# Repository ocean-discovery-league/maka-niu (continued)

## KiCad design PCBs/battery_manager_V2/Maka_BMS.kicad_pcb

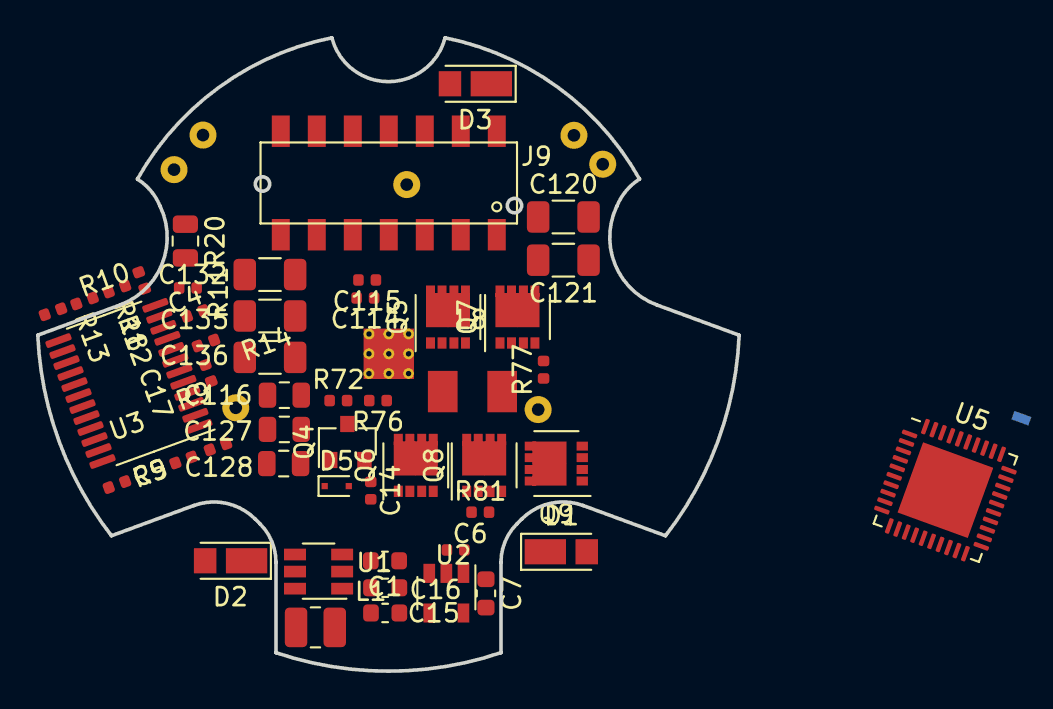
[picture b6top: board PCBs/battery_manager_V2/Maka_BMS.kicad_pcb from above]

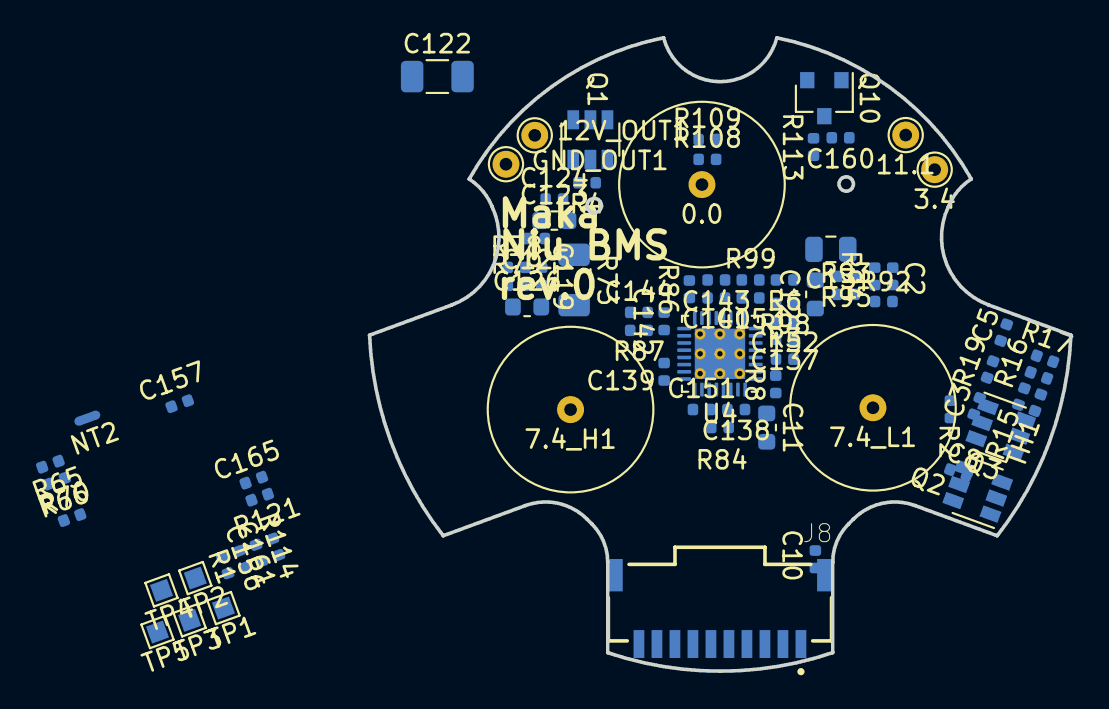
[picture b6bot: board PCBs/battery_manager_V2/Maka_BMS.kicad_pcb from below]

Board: 4 copper layers, 39.0 x 35.2 mm, 128 parts (79 on the bottom side), 89 nets, no tracks yet.

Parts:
0.0: 0; TruHole_Batter_Contact_Pad_with_9mm_clear
3.4: 3.4; TestPoint_THTPad_D1.5mm_Drill0.7mm
7.4_H1, 7.4_L1: 7.4; TruHole_Batter_Contact_Pad_with_9mm_clear
11.1: 11.1; TestPoint_THTPad_D1.5mm_Drill0.7mm
12V_OUT1: 12V_OUT; TestPoint_THTPad_D1.5mm_Drill0.7mm
C1, C15, C16, C123, C126: 10uF; C_0603_1608Metric
C2, C152, C153: 100pF; C_0402_1005Metric
C3, C4, C5, C10, C17, C119, C124, C156, C157: 0.1uF; C_0402_1005Metric
C6, C8, C9, C125, C137: 1uF; C_0402_1005Metric
C7: 4.7uF; C_0603_1608Metric
C11, C12: 0.033uF; C_0603_1608Metric
C13: 0.47uF; C_0805_2012Metric
C14, C138, C139: 0.047uF; C_0402_1005Metric
C114: 0.01uF; C_0402_1005Metric
C115, C160: 1000pF; C_0402_1005Metric
C116, C127, C128: 10uF; C_0805_2012Metric
C120, C136: 56uF; C_1206_3216Metric
C121, C122: 47uF; C_1206_3216Metric
C132, C135: 22uF; C_1206_3216Metric
C140: 33pF; C_0402_1005Metric
C142: 15pF; C_0402_1005Metric
C143: 1800pF; C_0402_1005Metric
C144: 680pF; C_0402_1005Metric
C151: 2.2uF; C_0402_1005Metric
C161, C165: 47pF; C_0402_1005Metric
D1, D2, D3: D_Schottky; D_SOD-123EP
D5: BAS5202VH6327; D_SC-79
GND_OUT1: GND_OUT; TestPoint_THTPad_D1.5mm_Drill0.7mm
J8: T1M-10-F-SH-L-K; SAMTEC_T1M-10-F-SH-L-K
J9: Molex 087340-1424; Molex_87340-1424_B
L1: 4.7uH; L_1008_2520Metric
L8: 2.2uH_Core_Iron; L_4.95x4.95_H2
NT2: Net-Tie_2; NetTie-2_SMD_Pad0.5mm
Q1, Q2, Q3: FDC645N; SOT-23-6_mosfet
Q4: BC817-16LT1G; SOT-23
Q5, Q6, Q7, Q8: CSD17308Q3; VSON-8_3.3x3.3mm_P0.65mm_NexFET
Q9: CSD25404Q3; VSON-8_3.3x3.3mm_P0.65mm_NexFET
Q10: DMG1012UW-7; SOT-23
R1, R16, R65, R66, R70, R95: 100K; R_0402_1005Metric
R2, R4, R5, R9, R13, R14, R19: 1K; R_0402_1005Metric
R3, R6: 4.99; R_0402_1005Metric
R8: 1; R_0402_1005Metric
R10, R15, R17, R87, R108, R109: 10K; R_0402_1005Metric
R11, R12: 1M; R_0402_1005Metric
R18: 470K; R_0402_1005Metric
R20: 0.02; R_0805_2012Metric
R72: 0.01; R_0402_1005Metric
R73: 0.01; R_1206_3216Metric
R76, R77, R81: 0; R_0402_1005Metric
R78, R79, R84, R114, R121: 10; R_0402_1005Metric
R86: 40.2K; R_0402_1005Metric
R92: 383K; R_0402_1005Metric
R93: 53.6K; R_0402_1005Metric
R94: 221K; R_0402_1005Metric
R98: 137K; R_0402_1005Metric
R99, R113: 30.1K; R_0402_1005Metric
TH1: 10K; R_0402_1005Metric
TP1: DSG_LED; TestPoint_Pad_1.0x1.0mm
TP2: BT1_LED; TestPoint_Pad_1.0x1.0mm
TP3: BT2_LED; TestPoint_Pad_1.0x1.0mm
TP4: BT3LED; TestPoint_Pad_1.0x1.0mm
TP5: BT4LED; TestPoint_Pad_1.0x1.0mm
U1: AP63205; TSOT-23-6
U2: TPS70933DBV; SOT-23-5
U3: BQ77915; TSSOP-24_4.4x7.8mm_P0.65mm
U4: BQ25703A_alt; Texas_S-PWQFN-N32_EP2.8x2.8mm_ThermalVias
U5: MSP430G2955IRHA40; Texas_S-PVQFN-N40_EP4.15x4.15mm

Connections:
+3.3VP: J9.7, Q10.2
+3V3: C7.2, C156.2, C157.2, J8.09, Q10.3, R65.2, R66.2, R108.1, R109.1, R113.2, U2.5, U5.14, U5.38, U5.39
+5V: C15.2, C16.2, J8.02, L1.2, U1.1
+BATT: 11.1.1, C119.2, C126.2, D2.2, R5.2, R9.2, R73.2, R79.2
-BATT: 0.0.1, C4.1, C5.2, C8.1, C9.2, R16.1, R17.1, R19.2, R20.2, TH1.1, U3.9, U3.10, U3.20, U3.23, U3.24
/A_EN: R70.2, U5.26
/BATDRVb: Q9.4, U4.21
/CHG_ACN: C114.2, C115.2, Q5.5, R3.2, R8.2, R72.1
/CHG_OK: R66.1, U4.4, U5.29
/CHG_PRC: R65.1, U4.11, U5.30
/CHG_SRN: R79.1, U4.19
/CHG_SRP: R78.1, U4.20
/COMP1: C140.2, R86.1, U4.16
/COMP2: C142.2, C144.2, U4.17
/DSG_EN: R1.1, U4.5, U5.12
/HB_HDV1: R76.2, U4.31
/HB_HDV2: R77.1, U4.24
/HB_HVDD1: C138.2, U4.30
/HB_HVDD2: C139.2, U4.25
/HB_LDV2: R81.1, U4.26
/HB_LG1: D5.1, Q4.1, U4.29
/HB_SW1: C138.1, L8.1, Q5.1, Q5.2, Q5.3, Q6.5, U4.32
/HB_SW2: C139.1, L8.2, Q7.1, Q7.2, Q7.3, Q8.5, U4.23
/IBAT: C153.2, U4.9, U5.7
/IPORT: C152.2, R98.2, U4.8, U5.6
/PSYS: R99.2, U4.10, U5.8
/REGN: C14.2, C151.2, Q4.3, R84.2, U4.28
/VDDA: C137.2, R84.1, R92.2, R93.2, U4.7
/VSYS: C120.1, C121.2, C122.2, C123.2, C124.2, Q7.5, Q9.5, U4.22
EN_3V3: Q10.1, U5.28
EN_5V0: U1.2, U5.40
EN_12V_G: R4.1, U5.3
EOC_KELLER: J8.05, J9.9
Earth: C1.1, C6.1, C7.1, C11.2, C12.1, C13.1, C14.1, C15.1, C16.1, C114.1, C115.1, C116.2, C120.2, C121.1, C122.1, C123.1, C124.1, C125.1, C126.1, C127.2, C128.2, C132.2, C135.2, C136.2, C137.1, C140.1, C142.1, C143.1, C151.1, C152.1, C153.1, C160.1, J8.01, J9.13, J9.14, NT2.2, Q1.3, Q3.3, Q6.1, Q6.2, Q6.3, Q8.1, Q8.2, Q8.3, R12.1, R18.1, R87.1, R98.1, R99.1, U1.4, U2.2, U4.14, U4.27, U4.33
GNDA: C156.1, C157.1, C161.1, C165.1, NT2.1, R1.2, R70.1, U5.1, U5.4, U5.13, U5.31, U5.41
GPS_INT: J8.07, J9.8
IMU_INT: J8.08, J9.10
unnamed: 3.4.1, R14.2
unnamed: 7.4_L1.1, R2.2
unnamed: 12V_OUT1.1, C1.2, C6.2, D1.1, D2.1, D3.1, U1.3, U2.1
unnamed: C2.1, R92.1, R94.2, U4.6
unnamed: C2.2, R94.1, R95.1
unnamed: C3.1, C4.2, R14.1, U3.7
unnamed: C5.1, R19.1, U3.8
unnamed: C8.2, R5.1, U3.1, U3.22
unnamed: C9.1, U3.2
unnamed: C10.1, L1.1, U1.5
unnamed: C10.2, U1.6
unnamed: C11.1, R3.1, U4.2
unnamed: C12.2, R6.1, U4.3
unnamed: C13.2, R8.1, U4.1
unnamed: C3.2, C17.1, R2.1, U3.6
unnamed: C17.2, R9.1, U3.3, U3.4, U3.5
unnamed: C119.1, C125.2, Q9.1, R73.1, R78.2
unnamed: C143.2, R86.2
unnamed: C144.1, R87.2
unnamed: D3.2, GND_OUT1.1, Q1.1
unnamed: D5.2, Q4.2, Q6.4
unnamed: Q1.2, R4.2
unnamed: Q2.1, Q3.1
unnamed: Q2.2, R10.1, R11.2
unnamed: Q2.3, R11.1, R20.1, U3.11
unnamed: Q3.2, R12.2, R13.1
unnamed: Q5.4, R76.1
unnamed: Q7.4, R77.2
unnamed: Q8.4, R81.2
unnamed: R10.2, U3.12
unnamed: R13.2, U3.13
unnamed: R15.1, TH1.2, U3.18
unnamed: R15.2, U3.19
unnamed: R16.2, U3.17
unnamed: R17.2, U3.16
unnamed: R18.2, U3.14
unnamed: R93.1, R95.2, U4.18
unnamed: R114.2, U5.11
unnamed: R121.2, U5.10
unnamed: TP1.1, U5.15
unnamed: TP2.1, U5.16
unnamed: TP3.1, U5.17
unnamed: TP4.1, U5.18
unnamed: TP5.1, U5.19
SBWTCK: J9.11, U5.37
SBWTDI: C160.2, J9.12, R113.1, U5.5
SCL: C161.2, J8.03, J9.5, R109.2, R114.1, U4.13
SDA: C165.2, J8.04, J9.6, R108.2, R121.1, U4.12
VBUS: C116.1, C127.1, C128.1, C132.1, C135.1, C136.1, D1.2, J9.1, J9.2, R6.2, R72.2
~INT~: J8.06, J9.3
~SHT_DWN_SIG~: J8.10, U5.36
~TS_EOC~: J9.4, U5.2

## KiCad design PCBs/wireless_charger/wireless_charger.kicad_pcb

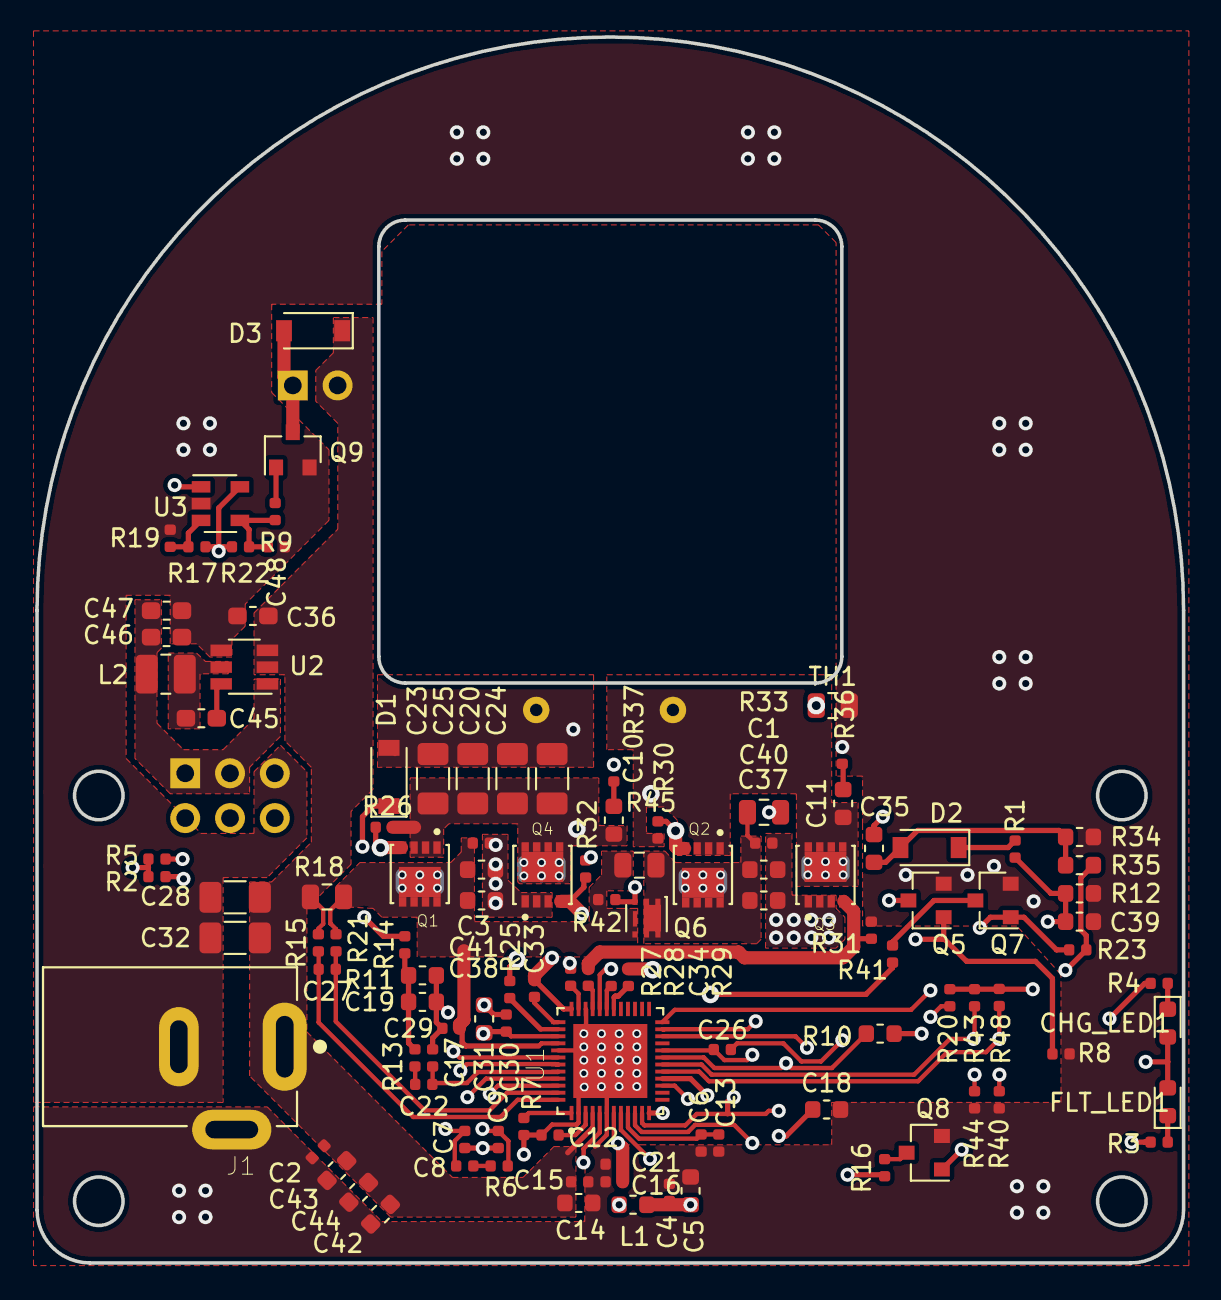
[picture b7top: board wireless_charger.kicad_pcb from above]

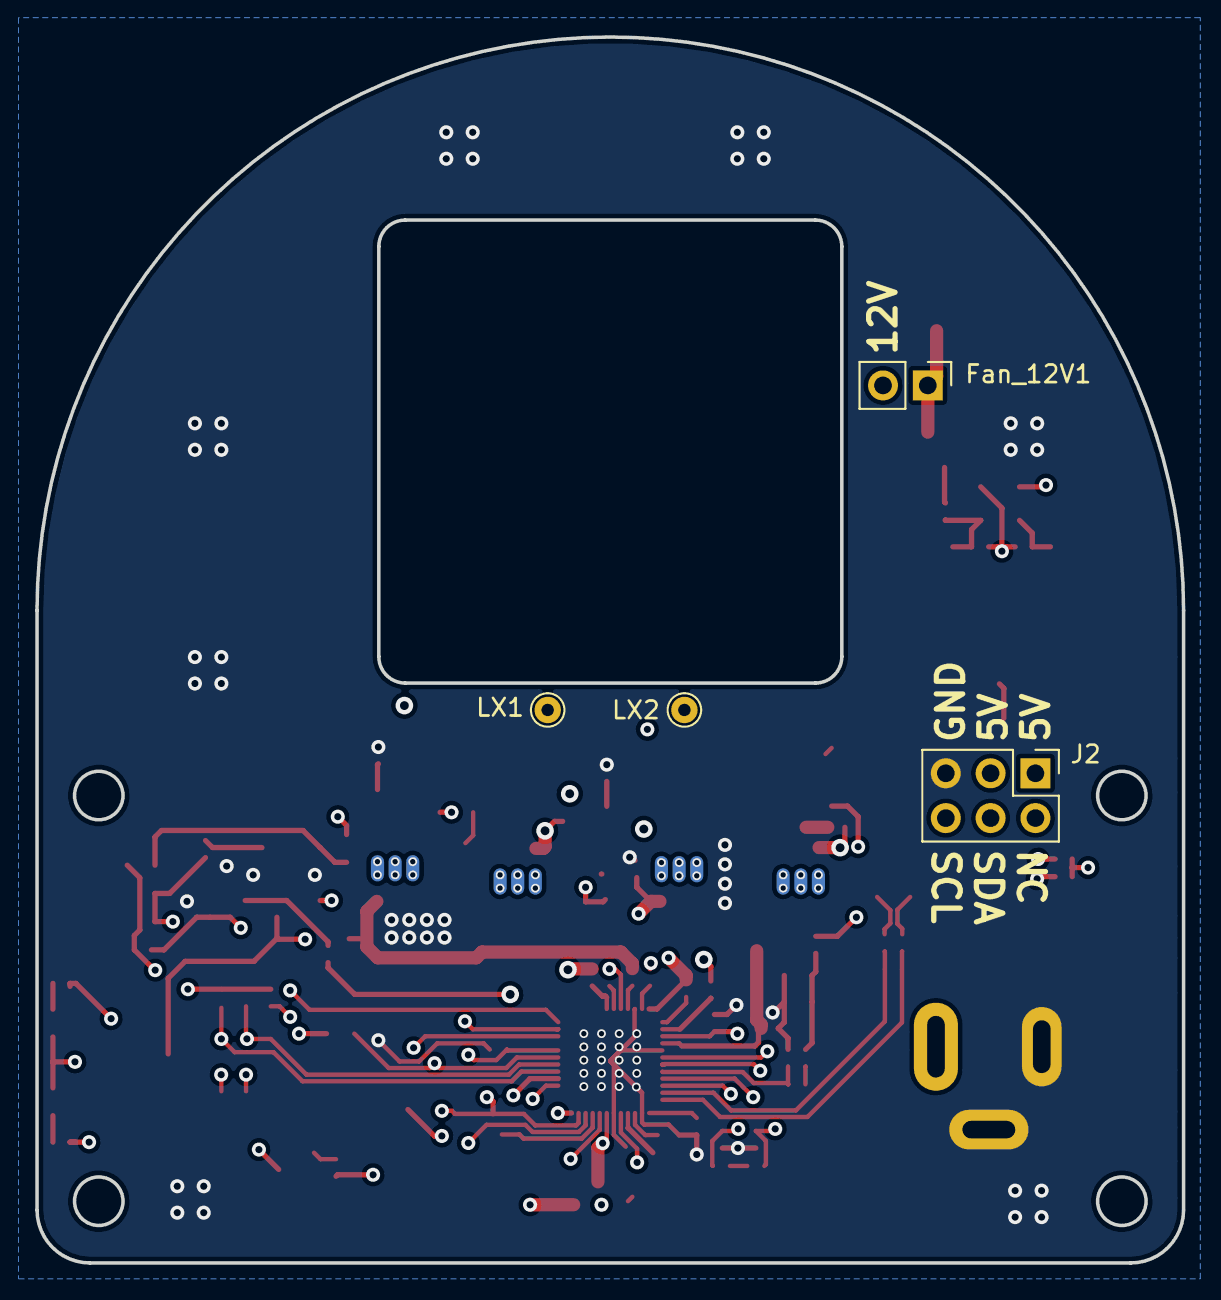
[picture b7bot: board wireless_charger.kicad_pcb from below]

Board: 4 copper layers, 65.0 x 69.5 mm, 116 parts (4 on the bottom side), 61 nets.

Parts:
C1, C2, C3, C4, C13, C15, C21, C26, C29, C30, C33, C34: 0.1uF; C_0402_1005Metric
C5, C14, C31, C37, C38, C40, C41: 10uF; C_0603_1608Metric
C6, C12, C16, C27: 1uF; C_0402_1005Metric
C7, C9: 56pF; C_0402_1005Metric
C8: 6.8nF; C_0402_1005Metric
C10, C11: 22nF; C_0603_1608Metric
C17: 680pF; C_0402_1005Metric
C18: 1nF; C_0603_1608Metric
C19, C35, C39: 5.6nF; C_0603_1608Metric
C20, C23, C24: 100nF; C_1206_3216Metric
C22: 22nF; C_0402_1005Metric
C25: 68nF; C_1206_3216Metric
C28, C32: 22uF; C_1206_3216Metric
C36, C46, C47: 10uF; C_0603_1608Metric_Pad1.05x0.95mm_HandSolder
C42: 0.1uF; C_0603_1608Metric
C43: 1uF; C_0603_1608Metric
C44: 4.7uF; C_0603_1608Metric
C45: 100nF; C_0603_1608Metric_Pad1.05x0.95mm_HandSolder
C48: 15pF; C_0402_1005Metric
CHG_LED1: GREEN; LED_0603_1608Metric
D1, D2: BAV21W; D_SOD-123
D3: MBR0530; D_SOD-123
FLT_LED1: RED; LED_0603_1608Metric
Fan_12V1: Conn_01x02; PinHeader_1x02_P2.54mm_Vertical
J1: Barrel_Jack_Switch; CUI_PJ-002AH
J2: Pi_Receiver; PinHeader_2x03_P2.54mm_Vertical
L1: 4.7uH; L_0603_1608Metric
L2: 4.7uH; L_1008_2520Metric
LX1, LX2: MountingHole_Pad; TestPoint_THTPad_D1.5mm_Drill0.7mm
Q1, Q2, Q3, Q4: DMG7430LFG; TRANS_DMP3017SFGQ-7_b
Q5, Q7, Q8: 2N7002; SOT-23
Q6: SiA453EDJ; Vishay_PowerPAK_SC70-6L_Single
Q9: NTR4003N; SOT-23
R1, R3, R7, R9: 1K; R_0402_1005Metric
R2, R5, R6, R13, R16, R19, R20, R22, R23, R41, R42, R43, R48: 10K; R_0402_1005Metric
R4: 680; R_0402_1005Metric
R8, R26, R30, R31, R32: 100K; R_0402_1005Metric
R10, R12: 390K; R_0603_1608Metric
R11, R35: 200K; R_0603_1608Metric
R14: 2.4K; R_0402_1005Metric
R15, R21: 10; R_0402_1005Metric
R17: 17.8; R_0402_1005Metric
R18: 0.02; R_0805_2012Metric
R25, R27, R28, R29: 12; R_0402_1005Metric
R33: 3; R_0805_2012Metric
R34: 100K; R_0603_1608Metric
R36, R37: 0.1; R_0402_1005Metric
R40: 14.3; R_0402_1005Metric
R44: 15.8K; R_0402_1005Metric
R45: 220; R_0805_2012Metric
TH1: 10K Thermistor; R_0805_2012Metric
U1: P9242-RNDGI8; QFN40P600X600X100-49N
U2: AP63205; TSOT-23-6
U3: LMV331; SOT-23-5

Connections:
+5V: C46.2, C47.2, J2.1, J2.3, L2.2, U2.1
/SCL: J2.6, R2.1, U1.15
/SDA: J2.4, R5.1, U1.16
/TS: C26.2, R20.2, TH1.1, U1.20, U3.1
/coil1: C11.2, C34.2, LX1.1, Q2.1, Q3.3, R30.1, U1.32
/coil2: C20.2, C23.2, C24.2, C25.2, C35.2, D1.2, LX2.1
Earth: C1.1, C2.2, C3.1, C4.1, C5.1, C6.1, C7.1, C9.1, C12.2, C13.1, C14.1, C15.1, C16.1, C17.1, C18.1, C19.1, C21.1, C26.1, C28.1, C29.1, C30.1, C31.1, C32.1, C36.1, C37.1, C38.1, C39.1, C40.1, C41.1, C42.2, C43.2, C44.2, C46.1, C47.1, C48.1, J1.2, J1.3, J2.5, Q3.1, Q4.1, Q5.2, Q7.2, Q8.2, Q9.2, R7.2, R8.1, R11.2, R12.2, R19.1, R31.1, R32.1, R34.2, R36.1, R37.1, R40.1, R44.1, TH1.2, U1.2, U1.6, U1.34, U1.41, U1.49, U2.4, U3.2
ISNS_H: C27.1, R15.1, U1.48
ISNS_L: C27.2, R21.1, U1.47
LDO18: C6.2, C13.2, U1.9
LDO33: C16.2, C21.2, CHG_LED1.2, FLT_LED1.2, R2.2, R5.2, R17.2, R20.1, R22.1, R23.2, R35.2, R43.2, R48.2, U1.7, U1.12, U3.5
unnamed: C1.2, C37.2, C40.2, Q2.3, Q6.1, R33.2, R45.1
unnamed: C7.2, C8.2, U1.45
unnamed: C8.1, R6.1
unnamed: C9.2, R6.2, U1.46
unnamed: C10.1, R37.2
unnamed: C10.2, C20.1, C23.1, C24.1, C25.1, C33.2, Q1.1, Q4.3, R26.1, U1.36
unnamed: C11.1, R36.2
unnamed: C12.1, U1.3
unnamed: C17.2, C22.1, U1.44
unnamed: C19.2, R11.1, R13.2, R14.1
unnamed: C22.2, R13.1
unnamed: C3.2, C29.2, C38.2, C41.2, Q1.3, Q6.4, R18.1, R21.2, R42.2, R45.2, U1.40
unnamed: C33.1, U1.37
unnamed: C34.1, U1.31
unnamed: C35.1, D2.2, R34.1, R35.1
unnamed: C39.2, R1.1, R10.1, R12.1
unnamed: C45.1, L2.1, U2.5
unnamed: C45.2, U2.6
unnamed: C48.2, R9.1, R22.2, U3.4
unnamed: CHG_LED1.1, R4.2
unnamed: D1.1, R14.2
unnamed: D2.1, R1.2
unnamed: D3.2, Fan_12V1.1, Q9.3
unnamed: FLT_LED1.1, R3.2
unnamed: L1.2, U1.5
unnamed: Q1.2, R25.1, R26.2
unnamed: Q2.2, R29.1, R30.2
unnamed: Q3.2, R28.1, R31.2
unnamed: Q4.2, R27.1, R32.2
unnamed: Q5.3, R33.1
unnamed: Q6.3, R41.2, R42.1
unnamed: Q7.3, R41.1
unnamed: Q8.3, R16.2
unnamed: Q9.1, R9.2
unnamed: R3.1, U1.10
unnamed: R4.1, U1.11
unnamed: R7.1, U1.1
unnamed: R17.1, R19.2, U3.3
unnamed: R25.2, U1.38
unnamed: R27.2, U1.35
unnamed: R28.2, U1.33
unnamed: R29.2, U1.30
unnamed: R40.2, R48.1, U1.17
unnamed: R43.1, R44.2, U1.18
OVP_CTL: Q8.1, U1.22
Q_DRV1: Q5.1, R8.2, U1.23
Q_DRV2: Q7.1, R23.1, U1.24
VCC_5V: C4.2, C5.2, C30.2, C31.2, L1.1, U1.8, U1.39
VCOIL_OV: C18.2, R10.2, R16.1, U1.19
VIN: C2.1, C14.2, C15.2, C28.2, C32.2, C36.2, C42.1, C43.1, C44.1, D3.1, Fan_12V1.2, J1.1, R15.2, R18.2, U1.4, U2.2, U2.3

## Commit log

2020-06-24 Lui's first commit, addign a python script to record video on the Pi Zero with aa camera module, with timestamp overlay. This could be used in Maka Niu to overlay temperature, depth etc. Also adding 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
2020-06-24 reorganized directory for future use
2020-07-07 Add files via upload
    Uploads a specified file to Tator
2020-07-07 Add files via upload
    Bash file to upload all mp4 files in directory (Calls TatorUpload.py with given arguments)
2020-07-13 added the kellerLD library, and a version of the example with a depth estimation based on pressure.
2020-07-17 Added a more complex python program Mode_dial_with_button for testing the the new hall sensor ring togethr with the new dial lthat incorporates a button
2020-07-31 added XM1110_example.py and supporting library. Example gets NMEA data from XM1111 via I2C and updates class objects with relevant info.
2020-08-13 Added the hall ring magnetic dial Kicad project
2020-08-13 added the battery management board kicad project
2020-08-13 Icreased trace thickness and rerouted higher freq and power paths in the battery management board
2020-08-14 added documenation folder and pushed 1st Power Distribution Chart
2020-08-14 Updated index.php: can access program.php, upload w button
2020-08-14 Updated index.php w program.php link and upload button
2020-08-14 Scaffold of page for user programmed missions
2020-08-14 added the maka niu general build BOM, and the maka niu build guide
2020-08-14 Chart of the code for program.php
    Displays all of the possible code blocks user would want to create and the respective strings for use in translating into python, and the string used to display html components
2020-08-14 changed current sensing resistor values on the BMS board to appropriately trip short and over current situations, adn to appropriately end incomig charge
2020-08-18 assigned digikey part to every item in battery management schematic, and created BOM
2020-08-31 Add files via upload
    Visual Representation and estimation calculation
2020-08-31 Add files via upload
    Documentation for Visual Representation and estimation calculations
2020-09-03 adding in progress pcb design files for the charging Station
2020-09-22 completed the wireless charger PCB design as rev 0. bom is compiled
2020-09-25 minor updating on BOM organization
2020-09-25 safety merge
2020-10-02 adding LED patterns simplified.
2020-10-22 first attempt at adding RPiCWI as a submodule
2020-10-23 added makaniu BMS board V2, and wayfinders 6cell BMS.
2020-11-22 Added haptic feedback to the Mode Dial python script
2020-11-22 updates to battery managemennt wayfinder boards, and makaniu hall sensor ring and BMS
2020-11-23 Fine of haptic feedback. new click, double click, burst, and dial change incorporated
2020-11-23 bit more fine tuning on haptic feedback. The clicks are nicer, but too hard notice by feel. Hearing them gives the illusion that they are enough, but with noise canceling headphones on, I can barely 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
2020-12-04 added comments for GPIOS
2020-12-04 Minor notes on BMS pcb project
2020-12-04 added Maka Niu User Flowchart.pdf in documentation
2020-12-07 Added a program called MakaNiu.py that begins to pull and incroporate all the peripheral hardware. Mode and button control, GPS, and image and video capture all working
2021-01-15 commented out drv vibration code because it causes crash if device not present
2021-01-18 MakaNiu.py program updated to include pressure info, as well as battery info, although it is disabled due to instability
2021-01-18 Lengthened update time for GPS and pressure to once every ten seconds, so that it interferes less with button presses. Need to bring in threads maybe, thou mixing I2c is scary. Also added a program t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
2021-01-18 improved timing interference between buttons and all the i2c time
2021-01-18 added a shell script to run python program with error log
2021-01-21 added try format to keller i2c comms to avoid occasional crash.
2021-01-22 All interfaces now protected with try/except method to prevent crashes. Program will run if any of these are missing. If all is present and talking, at startup, a green LED will hold for 3 seconds. A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
2021-01-22 added crash protection on DRV haptic feedback i2c. now Pi runs even if no interface connected.
2021-01-22 added the error log save destination on git
2021-01-25 Due to a a sepcific startup issue that emerged with introduciton of spi1, the shutdown pin has been switched with the enable endcap pin. Also added the enable endcap feature.
2021-01-26 added green light flash for GPS fix
2021-02-02 Incorporated date time from GPS. Required some changes in the gps libraries.
2021-02-02 Add files via upload
    Silkscreen modified for production
2021-02-02 Add files via upload
    Updated silkscreens
2021-02-02 Add files via upload
    Finalized for production
2021-02-02 Add files via upload
    added documentation for endcap PCB
2021-02-02 incorporated ability to name image files
2021-02-04 sped up shut down sequence
2021-02-05 added crash prptection with try for gps data
2021-02-05 added Pi video file naming, and added serial number to img and video naming.
2021-02-12 added sensor data file creation for videos
2021-02-12 heavy addition and cleanup of comments
2021-02-13 added creation of data file in missions
2021-02-13 added sensor data saving for images and burst images. Addressed a bug where burst photos also start a video.
2021-02-15 Added system clock entry in the sensor data files so that the separate mission manager program can easily read entry time
2021-02-17 implemented rotating data and error logging
2021-02-18 Added IMU sensor data collection and write to sensor files
2021-02-19 added battery power indication in wifi mode when battery pressed
2021-02-22 added use of pi os hostname in filenaming
2021-02-22 removed import of makaniu_config.py for now, not currently used
2021-02-22 sensor file writing now has has flush built into every print to update the files faster, and mode changes are written to a status file in log directory for easy read by other running software
2021-02-23 software/hardware fix of imu address bug. pin address was floating in hardware, so hardware fix sets the address to 0x69. Software follows the correction
2021-02-24 fixed datestamp for special case gns2 data in photo captures
2021-02-25 updated the repo with all latest pcb changes for the 6cell bms, 3cell bms, and for the wireless charger. Also added sensor data readme filein the same directory as the makaniu python program
2021-04-04 disabled led and hdmi cuttoff after some time, till this feature is really needed feo deployment
2021-04-08 added device id and mac address data to the top of each generated sensor file
2021-05-17 converted to non-dos eols, flush stdout on upload progress reports
2021-05-21 hacked in support for uploading attachments
2021-05-21 added link to attachments upload tutorial
2021-05-25 upload to folder named by hostname
2021-05-26 Reinstated LED and HDMI shutdown for poer saving, and reduced burst photo rate to 2hz to sidestep a bug that caused missing thumbnail images
2021-07-08 implemented keller depth offset background calibration that uses gps fix as reference for 0 depth.
2021-07-08 implemented clock update from gps even without a fix. Also disabled wifi in non wifi modes for power saving
2021-11-17 created a script locker folder to hold code that needs to be manually copied to other places. Also upgraded the wifi disbale code to close the access point.
2021-11-17 code version print changed to 1.03, to make it a little easier to track if users are up to date
2021-12-10 added a dimmensioned drawing of the Maka Niu Housing in the documentation section
2021-12-11 minor correction to a dimenisions pdf drawing of the enclosure
2021-12-17 correction to dimensioned diagram
2022-01-22 added a more files to the script_locker of code that needs to copied to directories outside the git project
2022-01-29 makaniu.py has minor edits. big one is keeping wifi enabled in non wifi mode if camera is believed to be above water
2022-02-01 removed outdated battery manager schematic
2022-02-01 changed voltage ranges for feedback so that the full charge 5 flashes are more likely to show on a full charge
2022-02-02 revised battery level visual feedback threshold voltages again based on observed voltage over time for a full charge to full deplete mission
2022-02-03 rc.local in the scriptlocker made smarter. Now errors are appended to the error log, so that they can be reviewed in perpetuity
2022-02-14 implemeted basic verion printing with incremented commits
2022-02-14 corrected bug on version printing when the daemon is called from outside the git repo, such as on boot
2022-02-18 removed annotation over images and video by RPI cam interface
2022-04-25 check files by filename and skip uploading duplicate, switch to makaniu uploads account API token
2022-04-25 moved the TatorUpload.py script into the coconut repo
2022-06-15 added new pcb projects: hall_ring, pi_zero_shield, and batter_manager_V1.1
2022-07-05 number of PCBs for 2nd round of Maka Niu fabrication, in their state after orders made.
2022-07-07 added a code sample for a great passive buzzer controller
2022-07-17 changes to MakaNiu to make it resilient to bad keller offset value on start up. Also slight change to how the ofset is calucalted, by adding the variable uncalibrated depth.
2022-07-29 added beginnig of MakaNiu LED ligth code with quality PWM control
2022-07-30 got MakaLED to work with the dial
2022-07-30 minor change to auto_copy_scripts so create startstop.sh next to startstopX.sh. Reason: pi interfaces seems to randomly revert back to startstop.sh, so we shouldnt use the X name anymore.
2022-08-05 added battery reading to MakaLED.py
2022-08-05 added battery level coutn in wifi button press for the flashlight code
2022-09-21 added a test python script for client side bluetooth
2022-09-21 added python script for testing bluetooth host side
2022-09-23 added the GNS2 line for videos. Till now, it was only given for images.
2022-10-25 added bluettooth LED module code. Still testing
2022-11-12 Changes to MakaNiu.py to accomodate new hardware, while still hopefully working on old hardware.
2022-11-19 more work on new hardware compatibility. Scripts added to setup units for either
2022-11-19 corrected IP address for LED version
2023-01-16 changed audio frequency to be audible outside of housing
2023-01-19 added method for Maka Niu to control LED module over bluetooth. An initial connection between two units must still be done manually over command line once, but afterwards units can be rebooted and th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
2023-01-19 cleaned up the LED module code quite a bit, removing some undefined/unusued variables, making it much more stable
2023-01-19 changed the trigger to attempt bluetooth connection to when getting batterly level. More user friendly
2023-01-19 revised how to retrieve bluetooth device name and address to. It now gets it diretly from the bluetooth hardware, rather than from a manual text file
2023-01-26 deleted the PCBs folder from the maka-niu project. That content has been moved to maka-ni-design-files project.
2023-02-01 a test branch created to easily disable the beep on Maka Niu units
2023-02-01 completely disabled pigpiod
2023-02-04 extended the no_beep branch to also not do haptic feedback. Testing if the haptic driver is somehow the issue for unit 0018, which seems to chrash, especially during photo burst
